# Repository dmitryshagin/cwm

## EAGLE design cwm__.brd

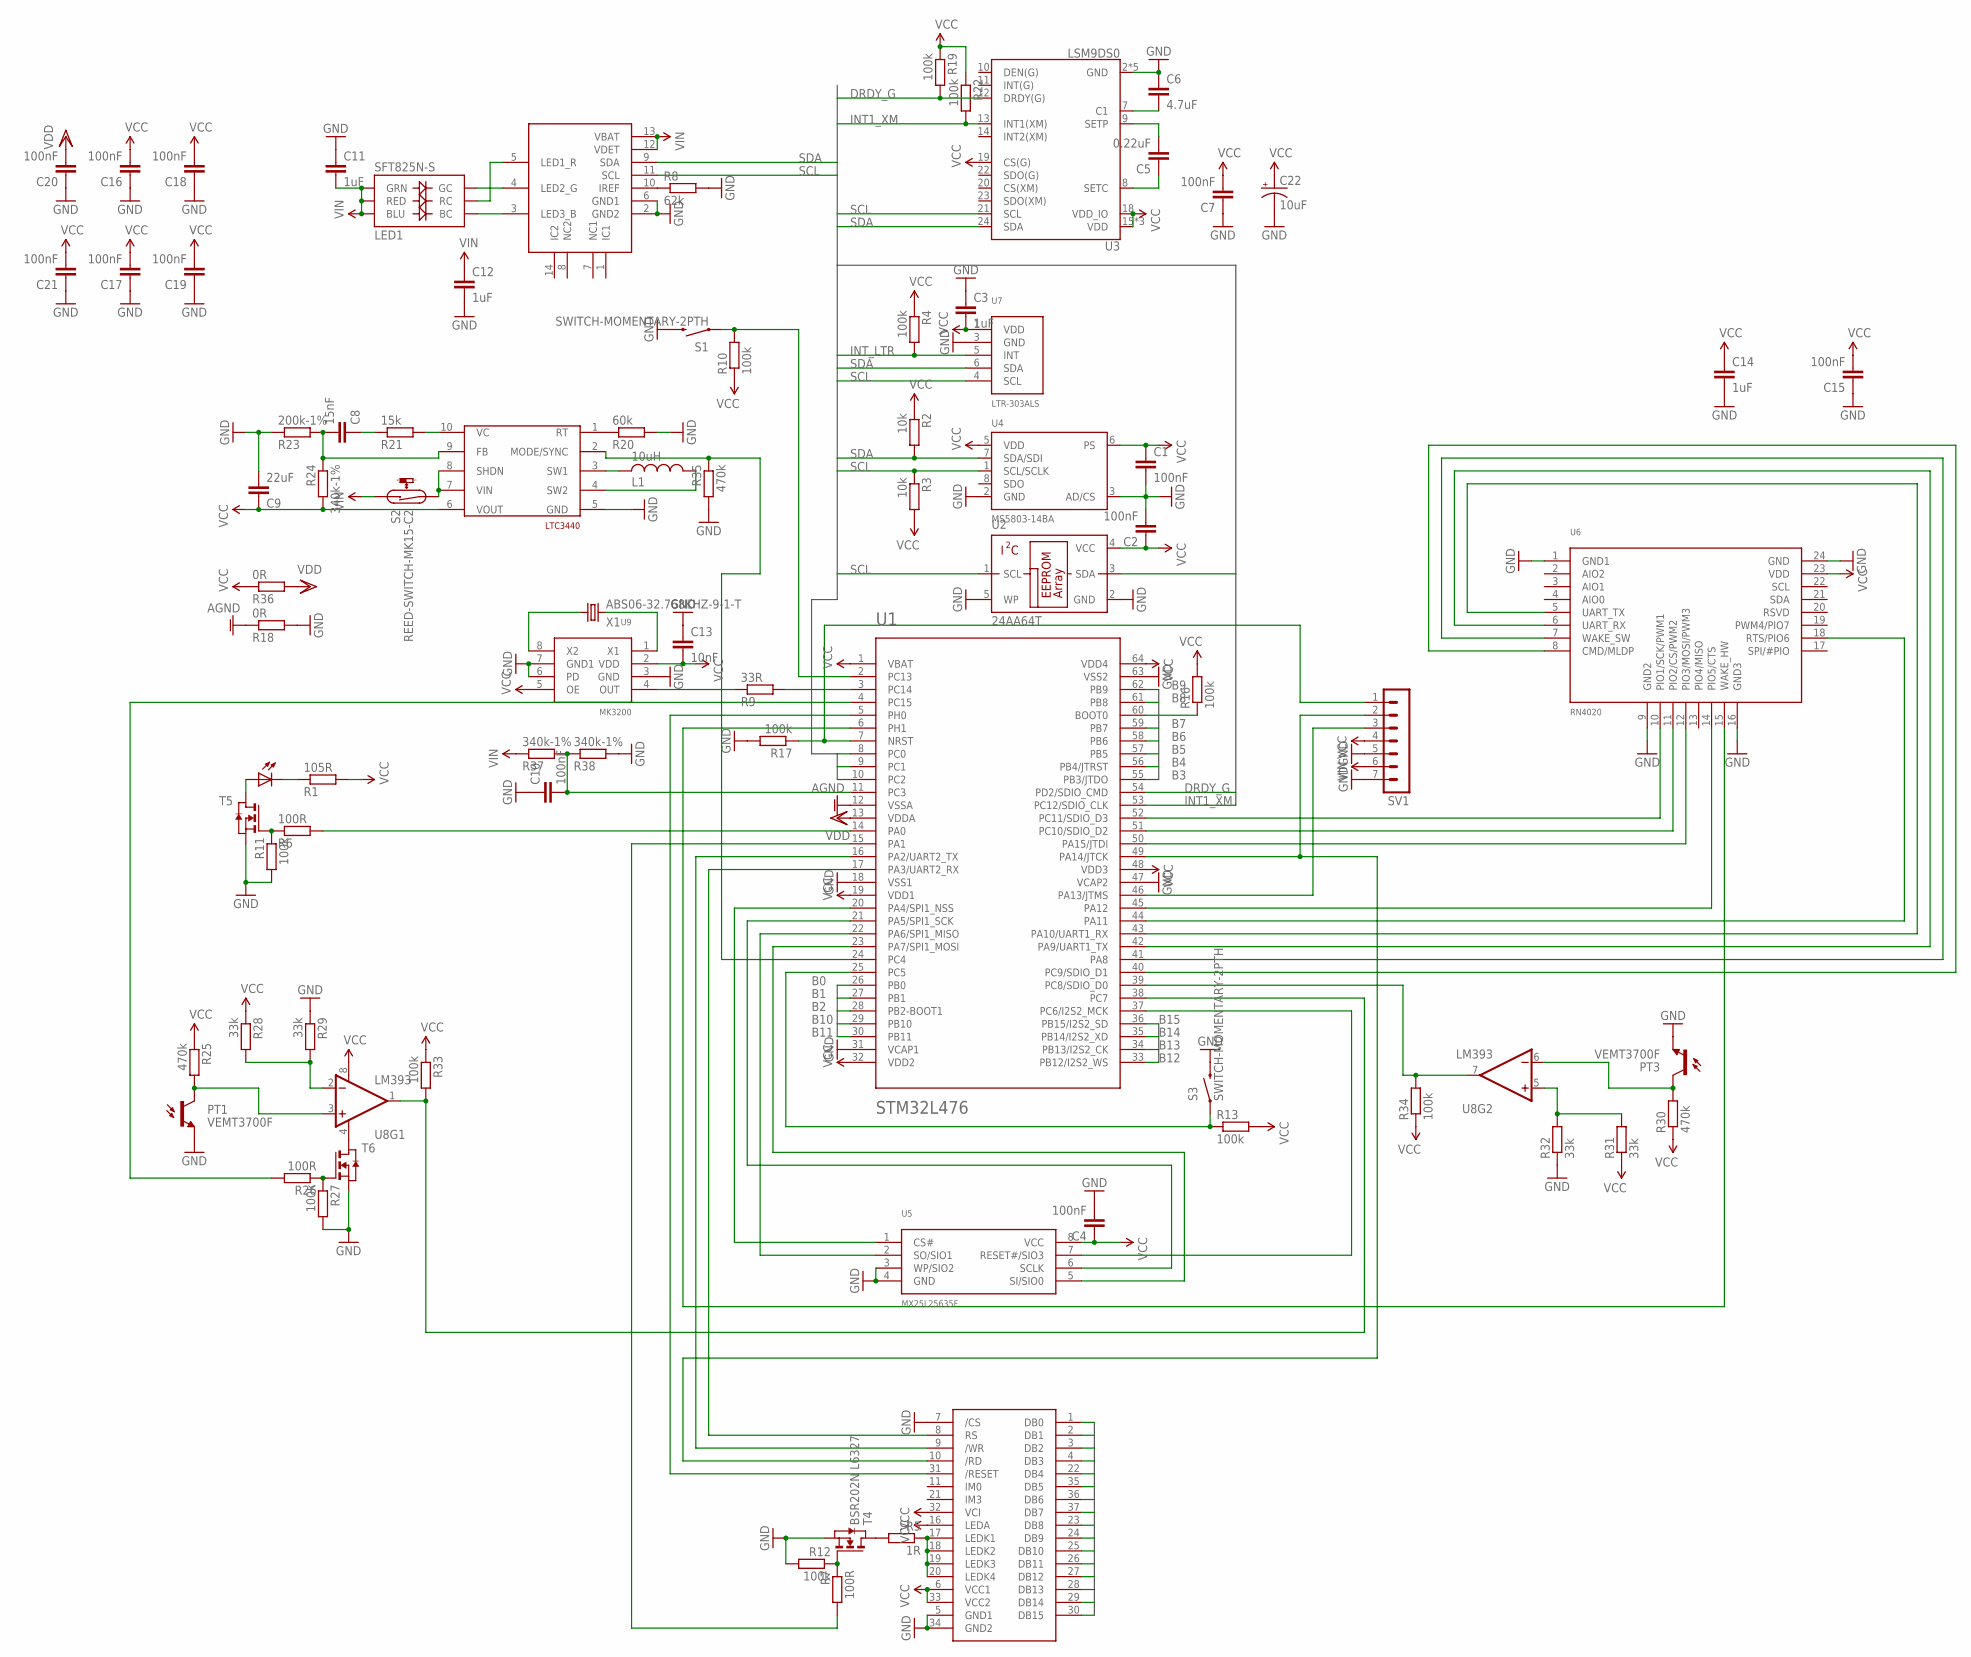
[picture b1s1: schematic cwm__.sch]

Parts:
C1, C2, C4, C7, C10, C15, C16, C17, C18, C19, C20, C21: 100nF; C0402
C3, C11, C12, C14: 1uF; C0603
C5: 0.22uF; C0402
C6: 4.7uF; C0805
C8: 15nF; C0402
C9: 22uF; C0805
C13: 10nF; C0402
C22: 10uF; A/3216-18R
L1: 10uH; L3225M
LED1: SFT825N-S; PLCC-6-LED
PT1, PT3: VEMT3700F; PLCC-2
R1: 105R; R0402
R2, R3: 10k; R0402
R4, R10, R11, R12, R13, R16, R17, R19, R22, R27, R33, R34: 100k; R0402
R5: 1R; R0402
R6, R7, R26: 100R; R0402
R8: 62k; R0402
R9: 33R; R0402
R18, R36: 0R; R0402
R20: 60k; R0402
R21: 15k; R0402
R23: 200k-1%; R0402
R24, R37, R38: 340k-1%; R0402
R25, R30, R35: 470k; R0402
R28, R29, R31, R32: 33k; R0402
S1, S3: SWITCH-MOMENTARY-2PTH; TACTILE-PTH
S2: REED-SWITCH-MK15-C2; MK15
SV1: MA07-1
T4: BSR202N L6327; SOT-23
T5, T6: NMOSSOT23; SOT-23
U1: STM32L476; TQFP64
U2: 24AA64T; SOT23-5L
U3: LSM9DS0; LGA-24
U4: MS5803-14BA; MS5803
U5: MX25L25635F; WSON8L
U6: RN4020
U7: LTR-303ALS
U8: LM393; SO08
U9: MK3200; SOIC8
U$1: S95466-AAA
U$2: VSML3710; PLCC-2
U$3: NCP5623
U$9: LTC3440; MSOP10
X1: ABS06-32.768KHZ-9-1-T; 2.0X1.2-2PAD

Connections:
AGND: R18.1, U1.12 (VSSA)
B0: U1.26 (PB0), U$1.1 (DB0)
B1: U1.27 (PB1), U$1.2 (DB1)
B2: U1.28 (PB2-BOOT1), U$1.3 (DB2)
B3: U1.55 (PB3/JTDO), U$1.4 (DB3)
B4: U1.56 (PB4/JTRST), U$1.22 (DB4)
B5: U1.57 (PB5), U$1.35 (DB5)
B6: U1.58 (PB6), U$1.36 (DB6)
B7: U1.59 (PB7), U$1.37 (DB7)
B8: U1.61 (PB8), U$1.23 (DB8)
B9: U1.62 (PB9), U$1.24 (DB9)
B10: U1.29 (PB10), U$1.25 (DB10)
B11: U1.30 (PB11), U$1.26 (DB11)
B12: U1.33 (PB12/I2S2_WS), U$1.27 (DB12)
B13: U1.34 (PB13/I2S2_CK), U$1.28 (DB13)
B14: U1.35 (PB14/I2S2_XD), U$1.29 (DB14)
B15: U1.36 (PB15/I2S2_SD), U$1.30 (DB15)
DRDY_G: R19.2, U1.54 (PD2/SDIO_CMD), U3.12 (DRDY(G))
GND: C1.2, C2.2, C3.1, C4.2, C6.1, C7.1, C9.2, C10.1, C11.1, C12.2, C13.1, C14.2, C15.1, C16.1, C17.1, C18.1, C19.1, C20.1, C21.1, C22.-, PT1.P$2 (E), PT3.P$2 (E), R8.2, R11.2, R12.2, R17.2, R18.2, R20.2, R23.1, R27.2, R29.1, R32.1, R35.2, R38.2, S1.3 (2), S3.3 (2), SV1.5, SV1.7, T4.2 (S), T5.2 (S), T6.2 (S), U1.18 (VSS1), U1.31 (VCAP1), U1.47 (VCAP2), U1.63 (VSS2), U2.2 (GND), U2.5 (WP), U3.2 (GND), U3.3 (GND), U3.4 (GND), U3.5 (GND), U3.6 (GND), U4.2 (GND), U4.3 (AD/CS), U5.3 (WP/SIO2), U5.4 (GND), U6.1 (GND1), U6.9 (GND2), U6.16 (GND3), U6.24 (GND), U7.3 (GND), U9.3 (GND), U9.6 (PD), U9.7 (GND1), U$1.5 (GND1), U$1.7 (/CS), U$1.34 (GND2), U$3.2 (GND2), U$3.6 (GND1), U$9.5 (GND)
INT1_XM: R22.2, U1.53 (PC12/SDIO_CLK), U3.13 (INT1(XM))
INT_LTR: R4.2, U1.10 (PC2), U7.5 (INT)
unnamed: S2.2, U$9.7 (VIN), U$9.8 (SHDN)
unnamed: R5.1, U$1.17 (LEDK1), U$1.18 (LEDK2), U$1.19 (LEDK3), U$1.20 (LEDK4)
unnamed: T5.1 (D), U$2.P$2 (A)
unnamed: C5.2, U3.9 (SETP)
unnamed: U1.6 (PH1), U6.15 (WAKE_HW)
unnamed: U1.17 (PA3/UART2_RX), U$1.8 (RS)
unnamed: U1.5 (PH0), U$1.31 (/RESET)
unnamed: U1.16 (PA2/UART2_TX), U$1.9 (/WR)
unnamed: R35.1, U1.24 (PC4), U$9.2 (MODE/SYNC)
unnamed: R5.2, T4.1 (D)
unnamed: LED1.CG (GC), U$3.4 (LED2_G)
unnamed: LED1.CB (BC), U$3.3 (LED3_B)
unnamed: LED1.CR (RC), U$3.5 (LED1_R)
unnamed: R1.1, U$2.P$1 (C)
unnamed: R6.1, R11.1, T5.3 (G)
unnamed: R6.2, U1.14 (PA0)
unnamed: R7.1, R12.1, T4.3 (G)
unnamed: R7.2, U1.15 (PA1)
unnamed: U9.1 (X1), X1.2
unnamed: R8.1, U$3.10 (IREF)
unnamed: U9.8 (X2), X1.1
unnamed: R9.1, U9.4 (OUT)
unnamed: SV1.2, U1.49 (PA14/JTCK), U$1.10 (/RD)
unnamed: R10.2, S1.1, U1.2 (PC13)
unnamed: R13.1, S3.1, U1.25 (PC5)
unnamed: R9.2, U1.3 (PC14)
unnamed: U1.42 (PA9/UART1_TX), U6.6 (UART_RX)
unnamed: L1.2, U$9.3 (SW1)
unnamed: L1.1, U$9.4 (SW2)
unnamed: C5.1, U3.8 (SETC)
unnamed: C6.2, U3.7 (C1)
unnamed: T6.1 (D), U8.4 (V-)
unnamed: PT1.P$1 (C), R25.2, U8.3 (+IN)
unnamed: R28.2, R29.2, U8.2 (-IN)
unnamed: R17.1, SV1.1, U1.7 (NRST)
unnamed: R16.1, U1.60 (BOOT0)
unnamed: PT3.P$1 (C), R30.2, U8.6 (-IN)
unnamed: R26.1, R27.1, T6.3 (G)
unnamed: R26.2, U1.4 (PC15)
unnamed: R31.2, R32.2, U8.5 (+IN)
unnamed: R33.2, U1.38 (PC7), U8.1 (OUT)
unnamed: R34.2, U1.39 (PC8/SDIO_D0), U8.7 (OUT)
unnamed: U1.43 (PA10/UART1_RX), U6.5 (UART_TX)
unnamed: U1.44 (PA11), U6.18 (RTS/PIO6)
unnamed: U1.45 (PA12), U6.14 (PIO5/CTS)
unnamed: U1.40 (PC9/SDIO_D1), U6.8 (CMD/MLDP)
unnamed: U1.41 (PA8), U6.7 (WAKE_SW)
unnamed: SV1.3, U1.46 (PA13/JTMS)
unnamed: U1.52 (PC11/SDIO_D3), U6.10 (PIO1/SCK/PWM1)
unnamed: U1.51 (PC10/SDIO_D2), U6.11 (PIO2/CS/PWM2)
unnamed: U1.50 (PA15/JTDI), U6.12 (PIO3/MOSI/PWM3)
unnamed: R20.1, U$9.1 (RT)
unnamed: U1.20 (PA4/SPI1_NSS), U5.1 (CS#)
unnamed: U1.22 (PA6/SPI1_MISO), U5.2 (SO/SIO1)
unnamed: U1.37 (PC6/I2S2_MCK), U5.7 (RESET#/SIO3)
unnamed: U1.21 (PA5/SPI1_SCK), U5.6 (SCLK)
unnamed: U1.23 (PA7/SPI1_MOSI), U5.5 (SI/SIO0)
unnamed: C10.2, R37.2, R38.1, U1.11 (PC3)
unnamed: C8.2, R23.2, R24.1, U$9.9 (FB)
unnamed: R21.2, U$9.10 (VC)
unnamed: C8.1, R21.1
SCL: R3.1, U1.8 (PC0), U2.1 (SCL), U3.21 (SCL), U4.1 (SCL/SCLK), U7.4 (SCL), U$3.11 (SCL)
SDA: R2.2, U1.9 (PC1), U2.3 (SDA), U3.24 (SDA), U4.7 (SDA/SDI), U7.6 (SDA), U$3.9 (SDA)
VCC: C1.1, C2.1, C3.2, C4.1, C7.2, C9.1, C13.2, C14.1, C15.2, C16.2, C17.2, C18.2, C19.2, C21.2, C22.+, R1.2, R2.1, R3.2, R4.1, R10.1, R13.2, R16.2, R19.1, R22.1, R24.2, R25.1, R28.1, R30.1, R31.1, R33.1, R34.1, R36.1, SV1.4, U1.1 (VBAT), U1.19 (VDD1), U1.32 (VDD2), U1.48 (VDD3), U1.64 (VDD4), U2.4 (VCC), U3.15 (VDD), U3.16 (VDD), U3.17 (VDD), U3.18 (VDD_IO), U3.19 (CS(G)), U4.5 (VDD), U4.6 (PS), U5.8 (VCC), U6.23 (VDD), U7.1 (VDD), U8.8 (V+), U9.2 (VDD), U9.5 (OE), U$1.6 (VCC1), U$1.16 (LEDA), U$1.32 (VCI), U$1.33 (VCC2), U$9.6 (VOUT)
VDD: C20.2, R36.2, U1.13 (VDDA)
VIN: C11.2, C12.1, LED1.AB (BLU), LED1.AG (GRN), LED1.AR (RED), R37.1, S2.1, SV1.6, U$3.12 (VDET), U$3.13 (VBAT)

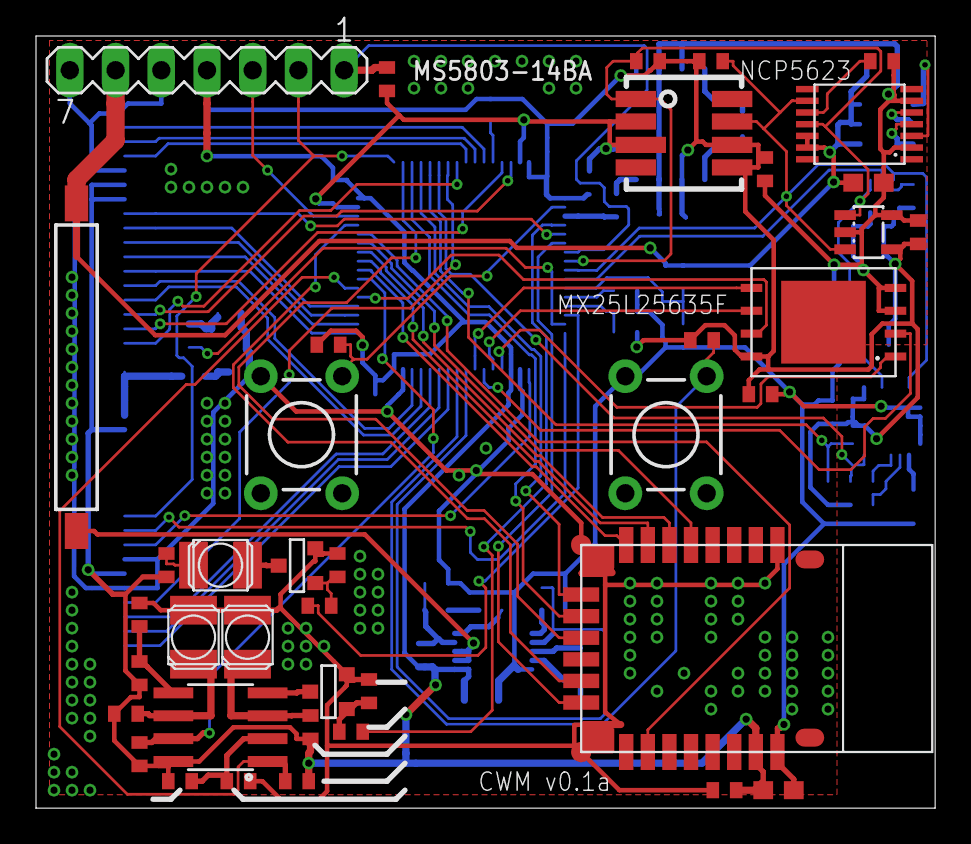
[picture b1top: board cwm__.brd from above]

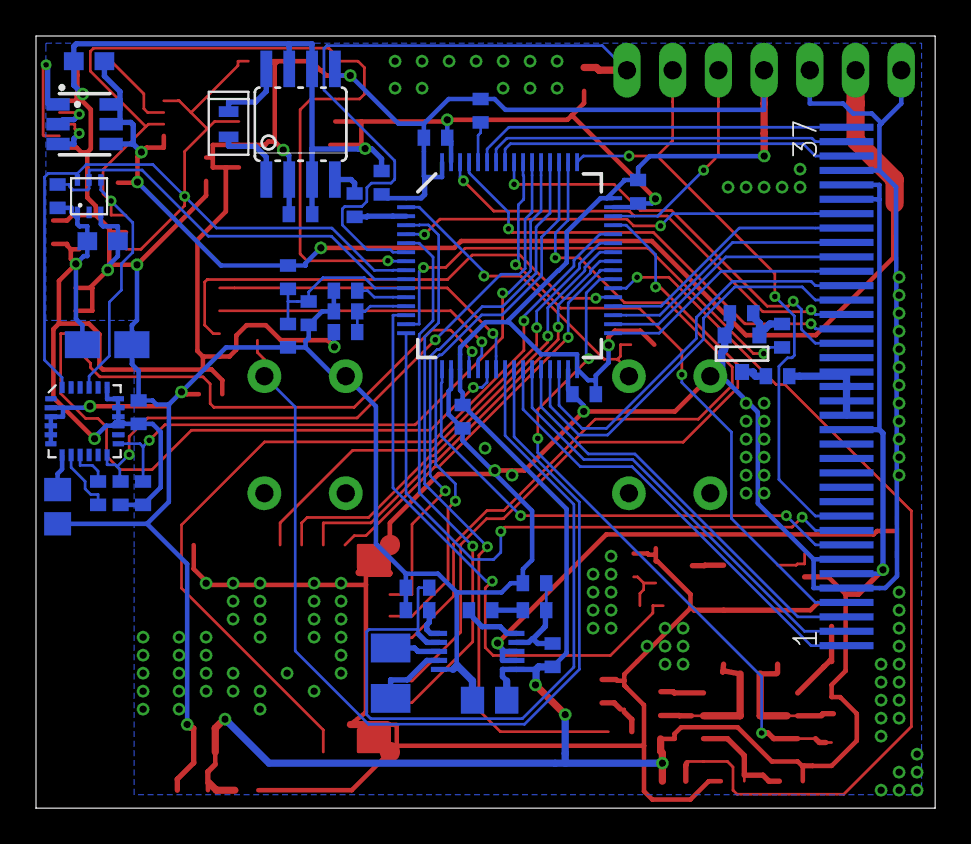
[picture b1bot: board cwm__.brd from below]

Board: 2 copper layers, 50.0 x 42.9 mm, 83 parts (43 on the bottom side), 87 nets.

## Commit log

2015-11-20 added all UCs
2015-11-20 some changes
2015-11-21 everything commected (draftely)
2015-11-21 added debuggin jack
2015-11-22 first steps for routing
2015-11-25 routed version 0.1a
2015-11-25 first gerbers generation
2015-11-25 updated gerbers

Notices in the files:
parts and their libraries:
SparkFun-DigitalIC: Licensing: Creative Commons ShareAlike 4.0 International - https://creativecommons.org/licenses/by-sa/4.0
